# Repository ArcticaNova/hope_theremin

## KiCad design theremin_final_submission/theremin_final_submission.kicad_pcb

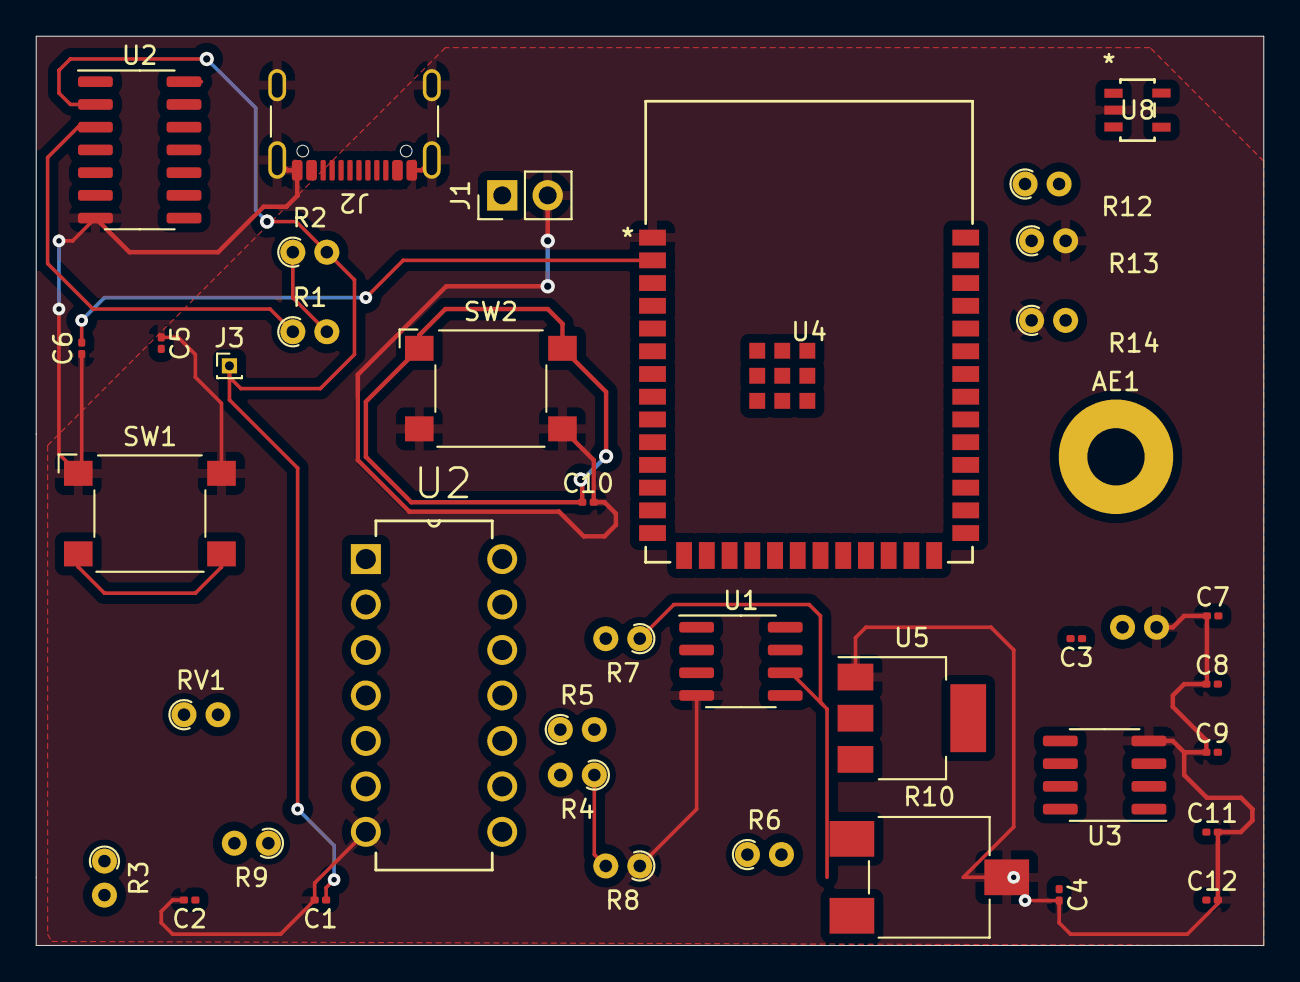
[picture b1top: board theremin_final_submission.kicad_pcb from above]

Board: 2 copper layers, 68.6 x 50.8 mm, 40 parts (1 on the bottom side), 24 nets.

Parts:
AE1: Antenna; MountingHole_3.2mm_M3_Pad
C1, C2: 100pF; C_0201_0603Metric
C3: 4.7uF; C_0201_0603Metric
C4: C; C_0201_0603Metric
C5, C6, C8: 1uF; C_0201_0603Metric
C7, C9, C10: .1uF; C_0201_0603Metric
C11: 100nF; C_0201_0603Metric
C12: 10uF; C_0201_0603Metric
J1: Conn_01x02_Pin; PinHeader_1x02_P2.54mm_Vertical
J2: USB_C_Receptacle_USB2.0; USB_C_Receptacle_GCT_USB4105-xx-A_16P_TopMnt_Horizontal
J3: Conn_01x01_Pin; PinHeader_1x01_P1.00mm_Vertical
R1, R3, R4, R5, R7, R8, R12: 10k; R_Axial_DIN0204_L3.6mm_D1.6mm_P1.90mm_Vertical
R2: 5.1k; R_Axial_DIN0204_L3.6mm_D1.6mm_P1.90mm_Vertical
R6: 6.8k; R_Axial_DIN0204_L3.6mm_D1.6mm_P1.90mm_Vertical
R9: 100k; R_Axial_DIN0204_L3.6mm_D1.6mm_P1.90mm_Vertical
R10: R_Trim; Potentiometer_ACP_CA6-VSMD_Vertical
R11: RM2012A-502_104-PBVW10; R_Axial_DIN0204_L3.6mm_D1.6mm_P1.90mm_Vertical
R13, R14: 5.1 k; R_Axial_DIN0204_L3.6mm_D1.6mm_P1.90mm_Vertical
RV1: 10k; R_Axial_DIN0204_L3.6mm_D1.6mm_P1.90mm_Vertical
SW1: Reset; SW_SPST_Omron_B3FS-100xP
SW2: Boot; SW_SPST_Omron_B3FS-100xP
U1, U3: AD8001AR; SOIC-8_3.9x4.9mm_P1.27mm
U2: HEF4093B; DIP254P762X420-14
U2#2: HEF4093B; SOIC-14_3.9x8.7mm_P1.27mm
U4: ESP32-S2-SOLO-N4R2; MOD41_ESP32-S2-SOLO_EXP
U5: LD1117S33TR_SOT223; SOT-223-3_TabPin2
U8: NCP164CSN330T1G; FP-NCP164CSN330T1G_OSI

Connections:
+3.3V: C8.2, C9.2, C12.1, R12.1, U5.2 (VO)
+5V: C11.1, J1.1, J2.A4 (VBUS), J2.A9 (VBUS), J2.B4 (VBUS), J2.B9 (VBUS), R11.1, U1.7 (V+), U2.14 (VCC), U2#2.1, U2#2.5, U2#2.14 (VCC), U3.7 (V+), U5.3 (VI)
/D+: J2.A6 (D+), J2.B6 (D+)
/D-: J2.A7 (D-), J2.B7 (D-)
GND: C1.2, C2.2, C4.2, C5.1, C6.1, C7.1, C8.1, C9.1, C10.2, C11.2, C12.2, J1.2, J2.A1 (GND), J2.A12 (GND), J2.B1 (GND), J2.B12 (GND), J2.S1 (SHIELD), R8.1, R10.2, R11.2, R13.2, R14.1, SW1.1, SW2.2, U1.4 (V-), U2.7 (GND), U2#2.7 (GND), U3.4 (V-), U4.1 (GND), U5.1 (GND), U8.2 (GND)
unnamed: AE1.1 (A), C1.1, J3.1, R2.2, U2#2.2
unnamed: C2.1, R3.2, U2.6, U2#2.6
unnamed: C3.2, C4.1, R6.2, R10.1
unnamed: J2.A5 (CC1), R13.1
unnamed: J2.B5 (CC2), R14.2
unnamed: R1.1, R5.1, U2.3, U2#2.3
unnamed: R1.2, R2.1
unnamed: R3.1, RV1.1
unnamed: R4.2, RV1.2, U2.4, U2#2.4
unnamed: R6.1, R7.1, U1.6
unnamed: R4.1, R8.2, U1.3 (+)
unnamed: R5.2, R7.2, U1.2 (-)
unnamed: U3.3 (+), U3.6
unnamed: C3.1, U3.2 (-), U4.5 (IO5)
unnamed: C6.2, R9.2, U4.2 (3V3), U8.5 (OUT)
unnamed: C7.2, R12.2, SW1.2
unnamed: C10.1, SW2.1
unnamed: C5.2, U8.1 (IN), U8.3 (EN)
unnamed: R9.1, U8.4 (PG)

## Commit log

2024-04-05 layout and sch
2024-04-11 fixed BoM
2024-04-12 almost there
2024-04-12 cleaned it up a bit
2024-04-12 BOM and some schematic updates
